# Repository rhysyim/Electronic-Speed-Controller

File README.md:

A hardware implementation using comparators to compare BEMF of motor in /PCB/Triple Half Bridge Driver v4b2. The original implementatoin with current sensing amplifier in /PCB/Triple Half Bridge Driver v4a (footprints not in place yet).

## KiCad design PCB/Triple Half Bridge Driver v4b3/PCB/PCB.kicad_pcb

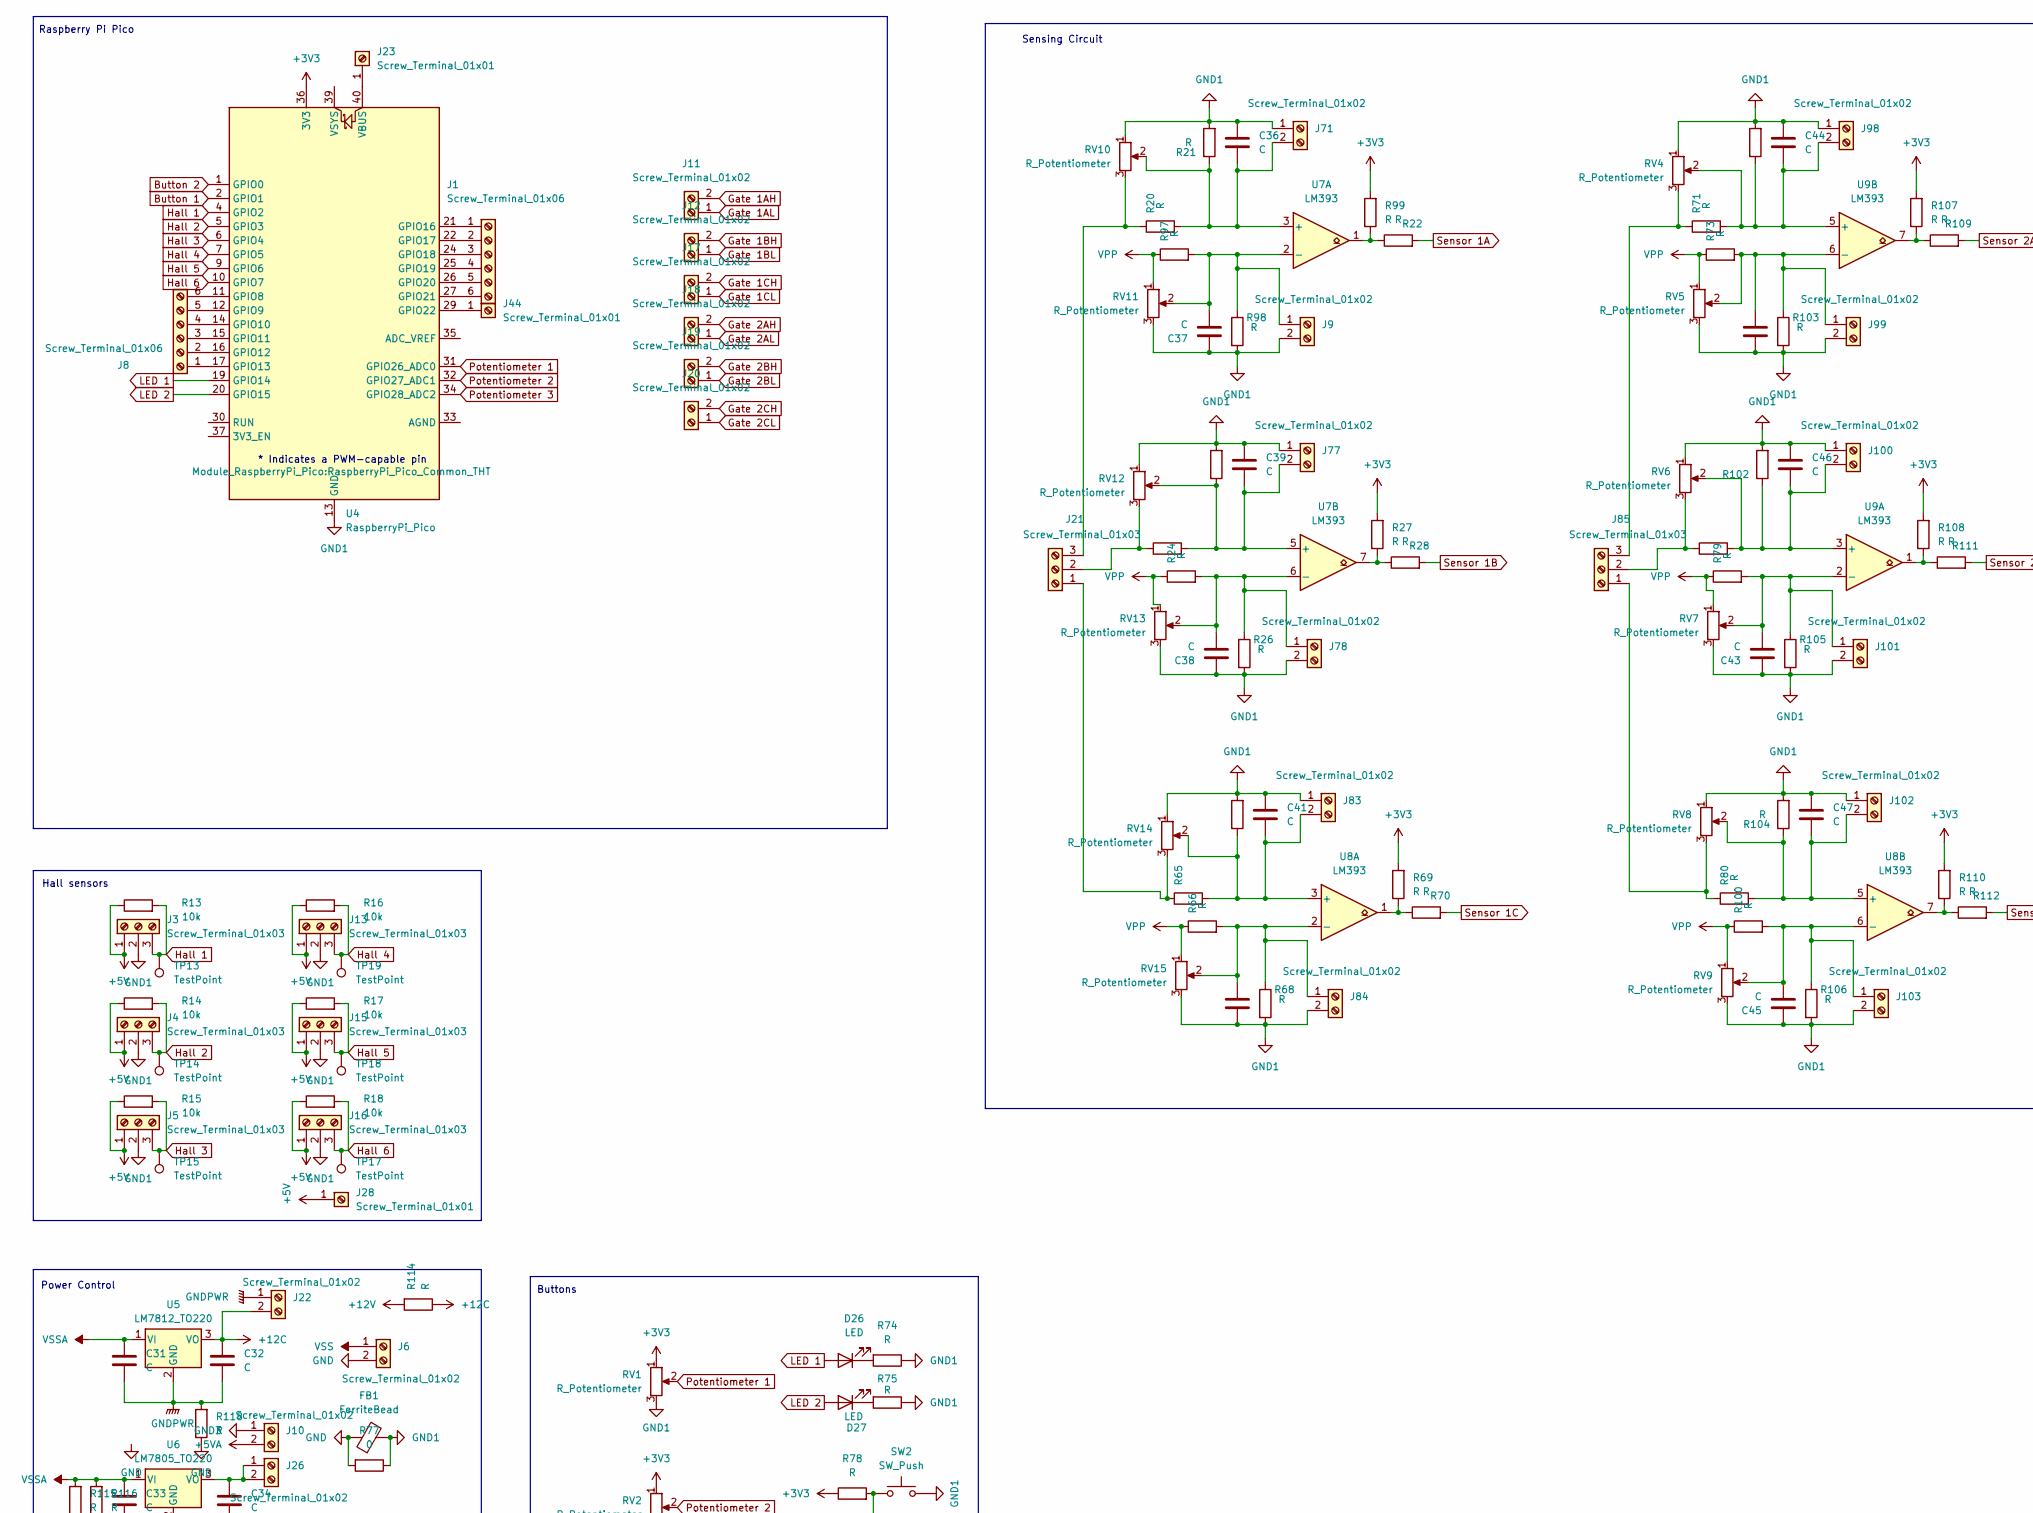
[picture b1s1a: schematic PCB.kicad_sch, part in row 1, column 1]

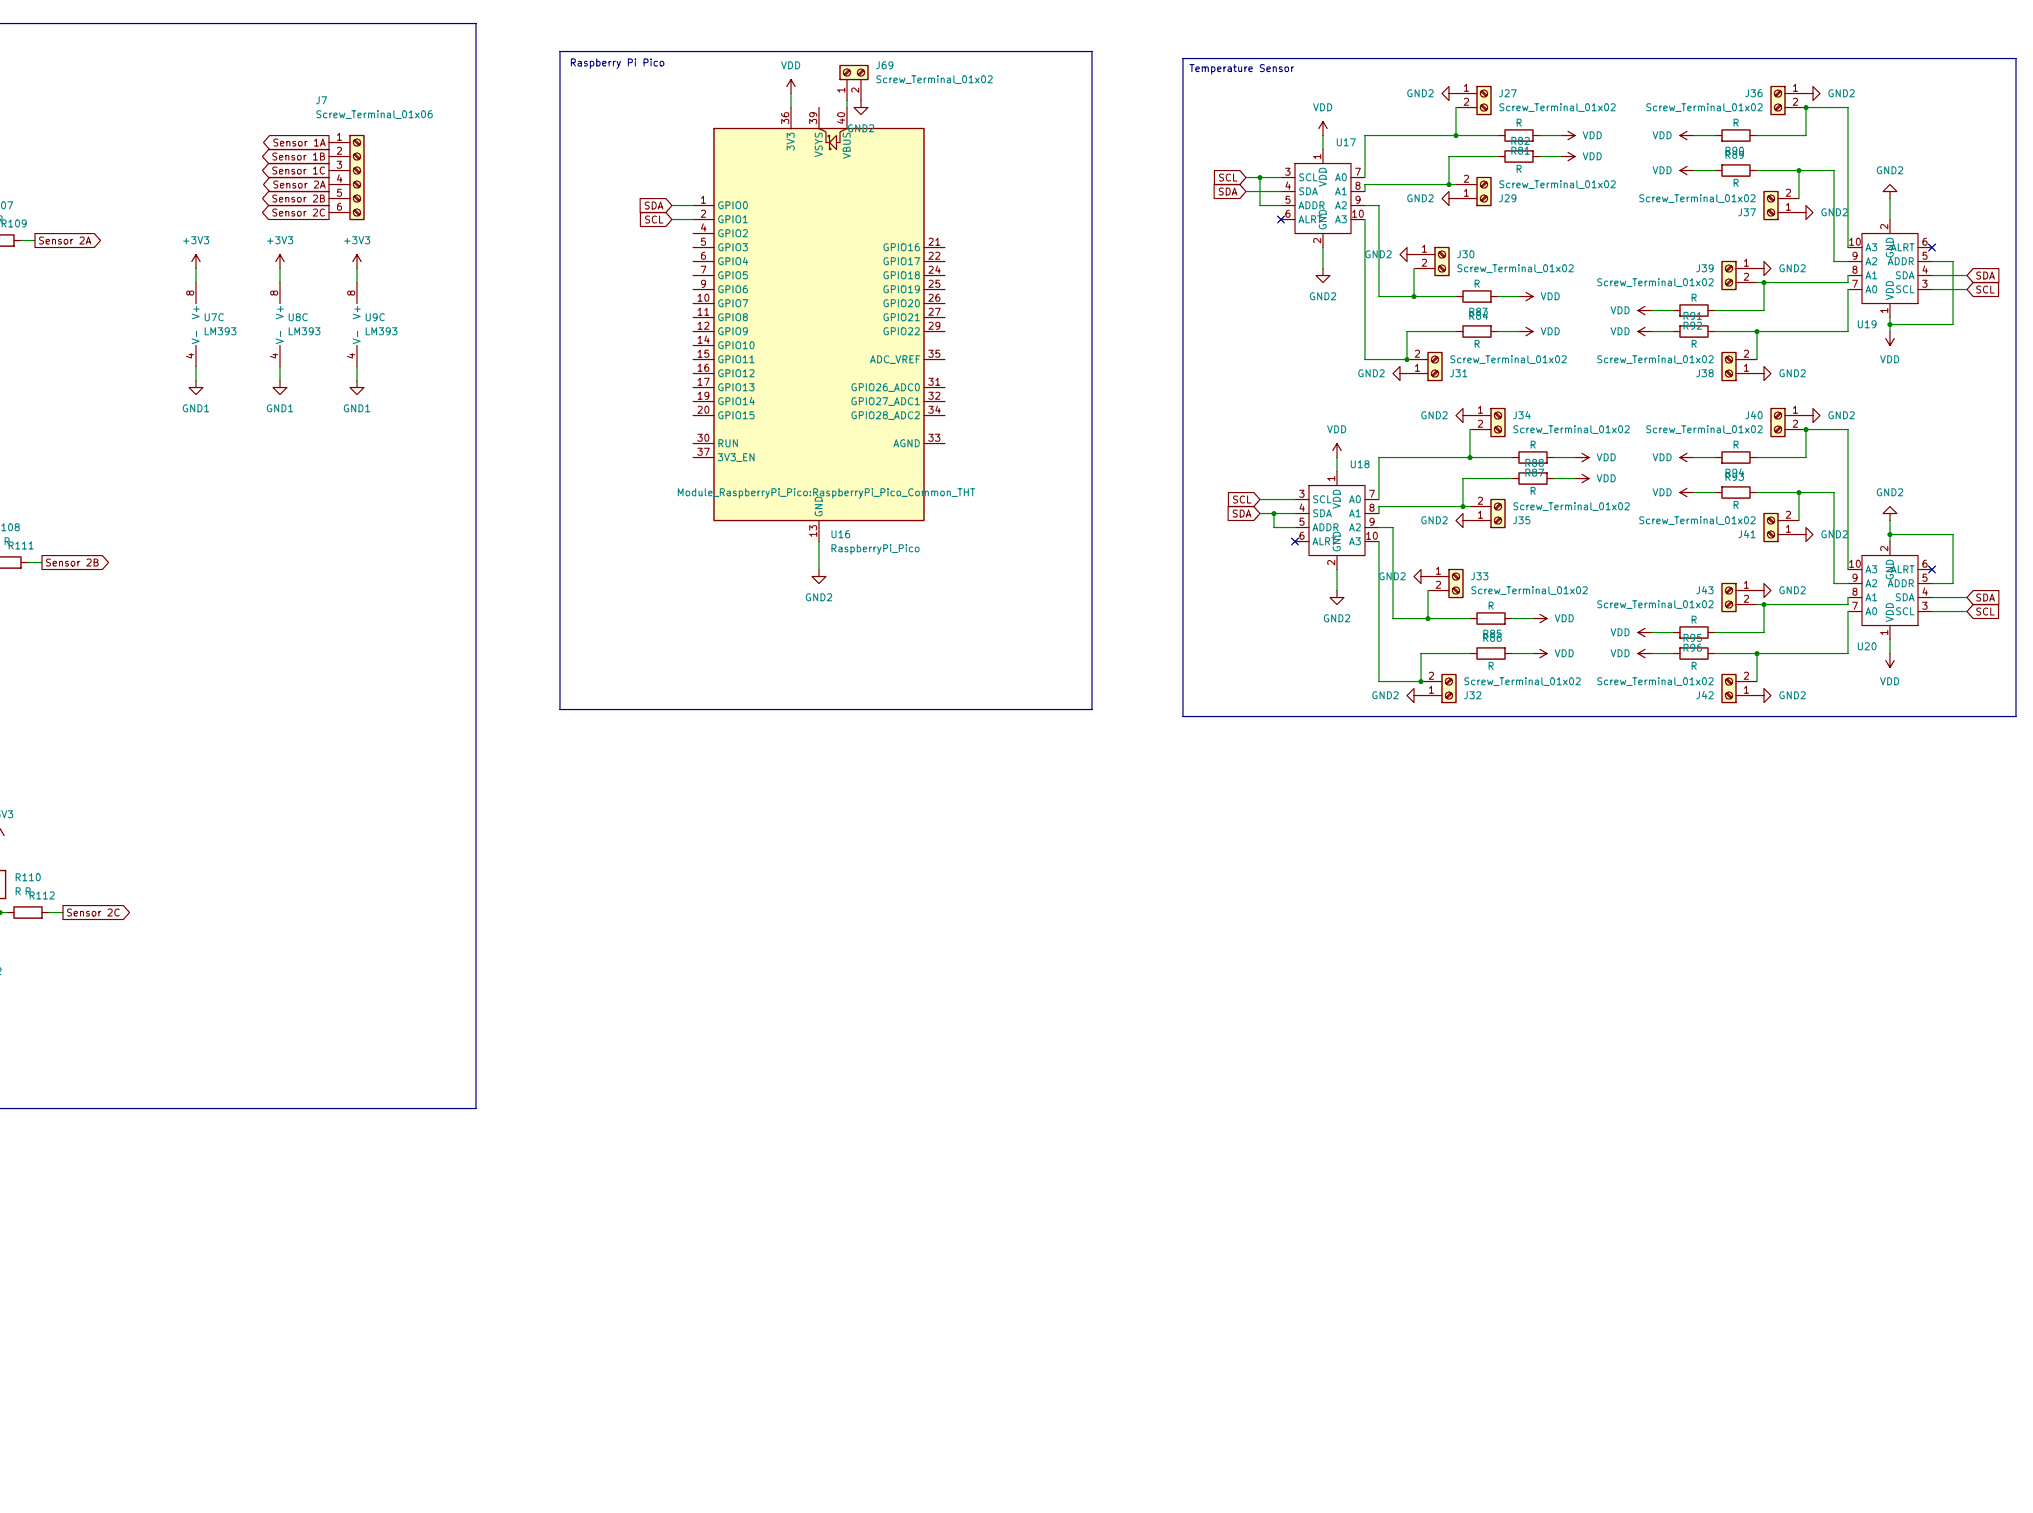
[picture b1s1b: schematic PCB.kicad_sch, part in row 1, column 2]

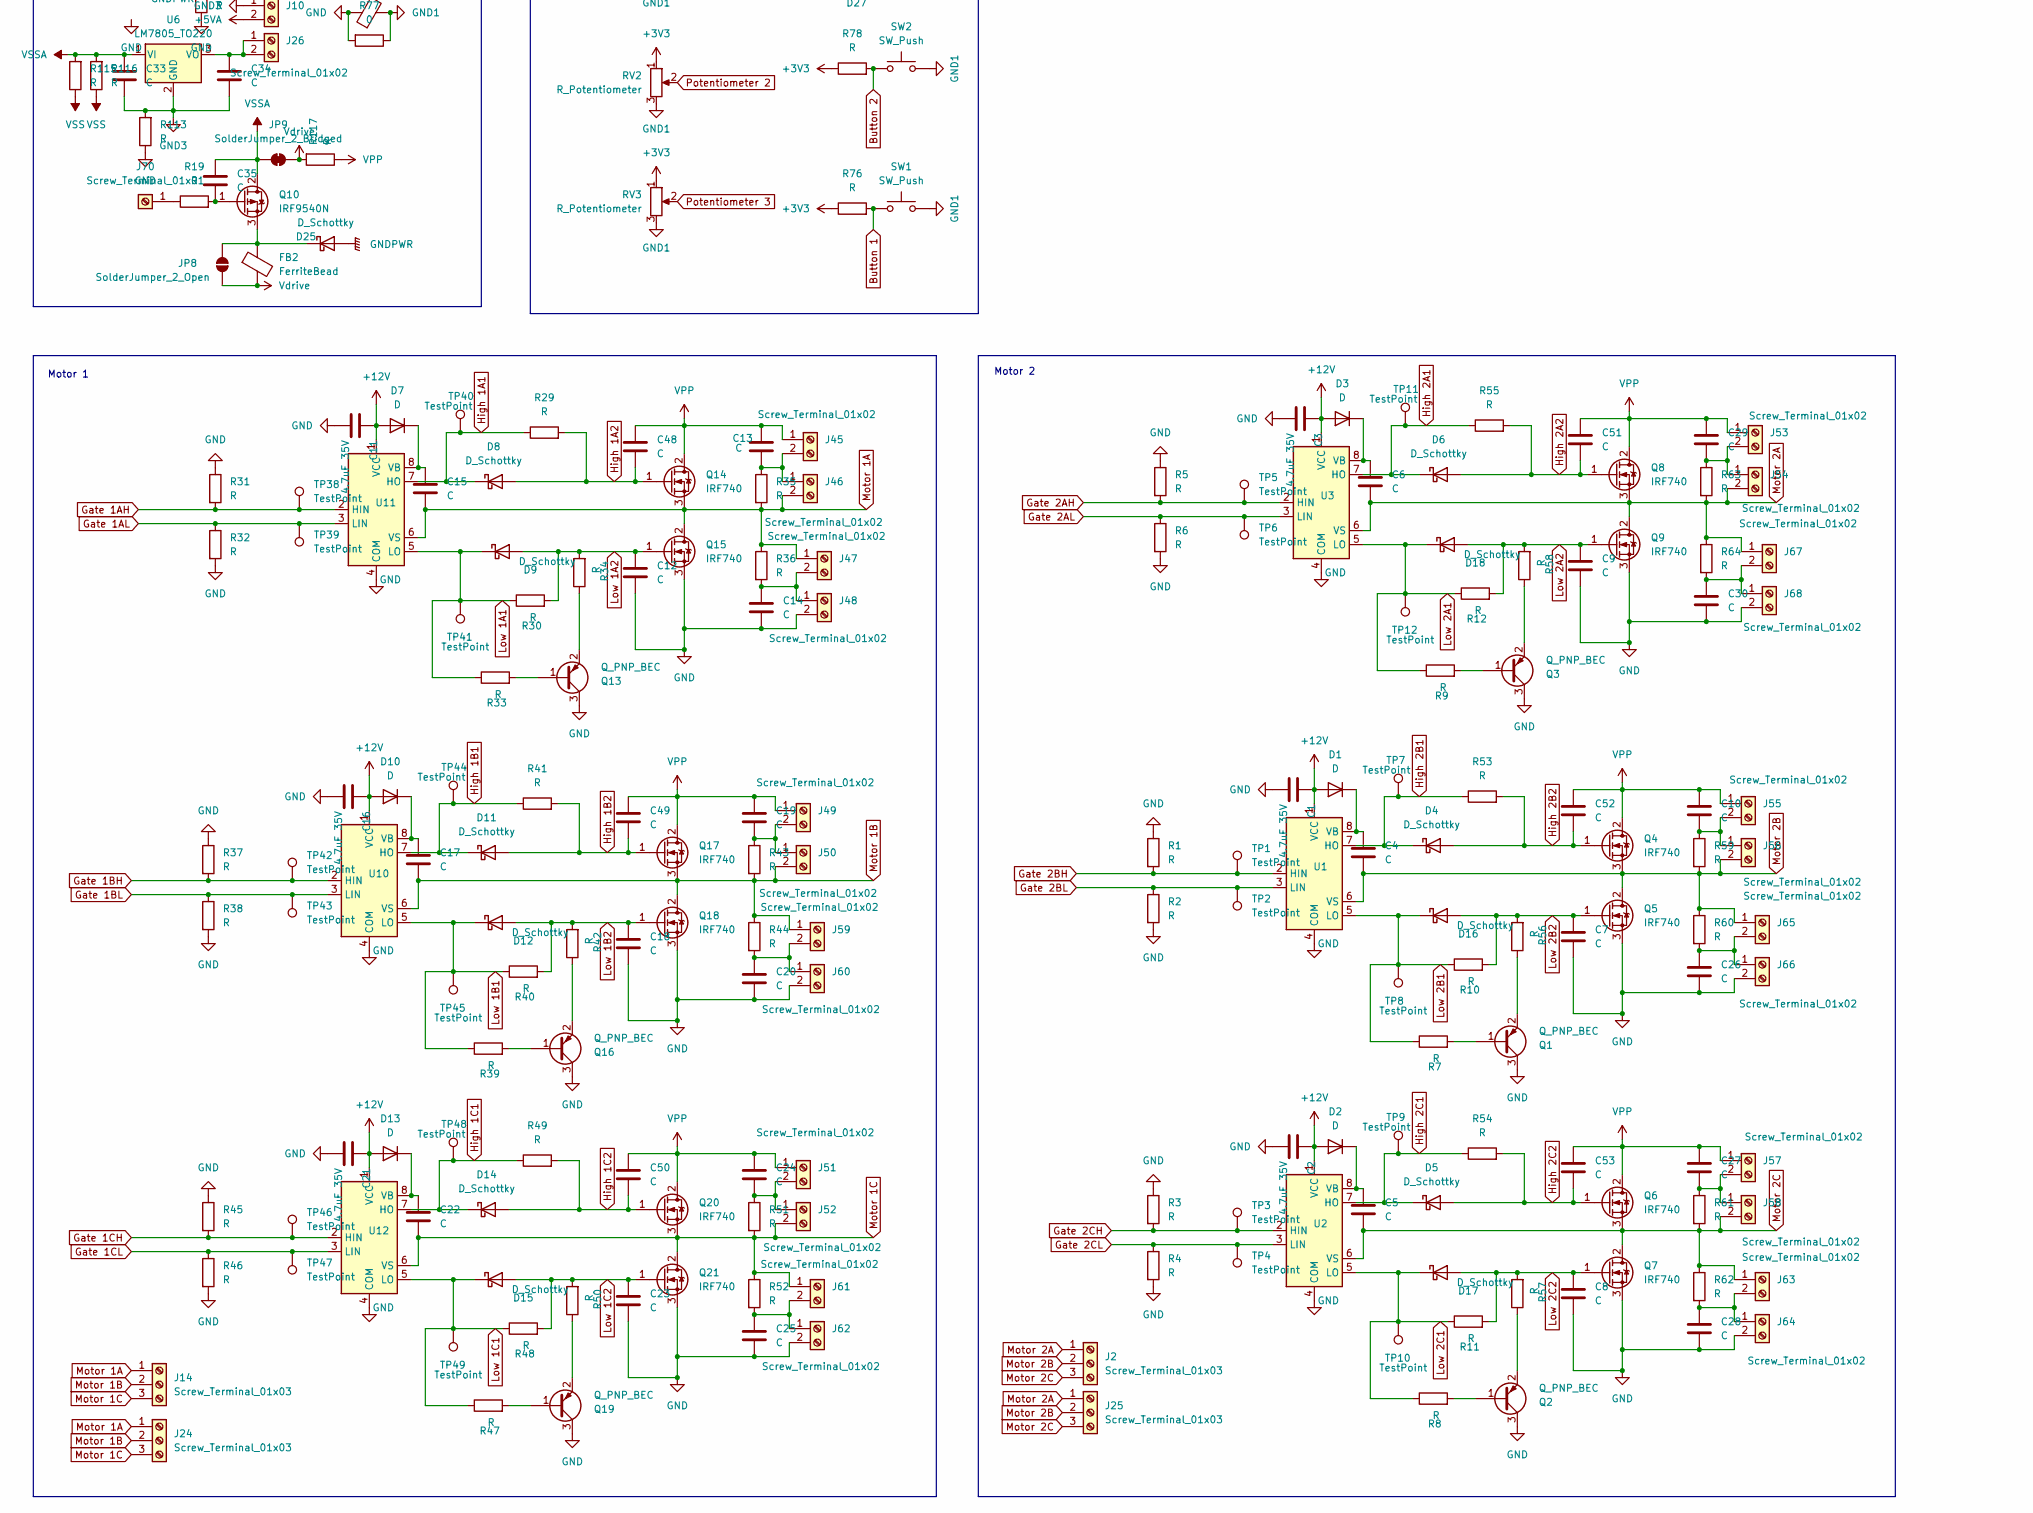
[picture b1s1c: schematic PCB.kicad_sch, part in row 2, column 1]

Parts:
C1, C2, C3, C11, C16, C21: 4.7uF 35V; C_Rect_L7.0mm_W4.5mm_P5.00mm; LCSC C162274
C4, C5, C6, C7, C8, C9, C10, C12, C13, C14, C15, C17, C18, C19, C20, C22, C23, C24, C25, C26, C27, C28, C29, C30, C31, C32, C33, C34, C35, C36, C37, C38, C39, C40, C41, C42, C43, C44, C45, C46, C47, C48, C49, C50, C51, C52, C53: C; C_Rect_L7.0mm_W4.5mm_P5.00mm
D1, D2, D3, D7, D10, D13: D; D_A-405_P7.62mm_Horizontal
D4, D5, D6, D8, D9, D11, D12, D14, D15, D16, D17, D18, D25: D_Schottky; D_A-405_P7.62mm_Horizontal
D26, D27: LED; LED_D5.0mm
FB1, FB2: FerriteBead; LairdTech_28C0236-0JW-10
J1, J7, J8: Screw_Terminal_01x06; PinHeader_1x06_P2.54mm_Vertical
J2, J14, J21, J24, J25, J85: Screw_Terminal_01x03; 1792876
J3, J4, J5, J13, J15, J16: Screw_Terminal_01x03; PinHeader_1x03_P2.54mm_Vertical
J6, J9, J10, J11, J12, J17, J18, J19, J20, J22, J69: Screw_Terminal_01x02; 1792863
J23, J44, J70: Screw_Terminal_01x01; PinHeader_1x01_P2.54mm_Vertical
J26: Screw_Terminal_01x02; PinHeader_1x02_P2.54mm_Vertical
J27, J29, J30, J31, J32, J33, J34, J35, J36, J37, J38, J39, J40, J41, J42, J43, J45, J46, J47, J48, J49, J50, J51, J52, J53, J54, J55, J56, J57, J58, J59, J60, J61, J62, J63, J64, J65, J66, J67, J68, J71, J77, J78, J83, J84, J98, J99, J100, J101, J102, J103: Screw_Terminal_01x02; TerminalBlock_4Ucon_1x02_P3.50mm_Horizontal
J28: Screw_Terminal_01x01; TerminalBlock_4Ucon_1x02_P3.50mm_Horizontal
JP8: SolderJumper_2_Open; SolderJumper-2_P1.3mm_Open_Pad1.0x1.5mm
JP9: SolderJumper_2_Bridged; SolderJumper-2_P1.3mm_Bridged_Pad1.0x1.5mm
Q1, Q2, Q3, Q13, Q16, Q19: Q_PNP_BEC; TO-220-3_Vertical; LCSC C686646
Q4, Q5, Q6, Q7, Q8, Q9, Q14, Q15, Q17, Q18, Q20, Q21: IRF740; TO-220-3_Vertical
Q10: IRF9540N; TO-220-3_Vertical
R1, R2, R3, R4, R5, R6, R7, R8, R9, R10, R11, R12, R19, R20, R21, R22, R23, R24, R25, R26, R27, R28, R29, R30, R31, R32, R33, R34, R35, R36, R37, R38, R39, R40, R41, R42, R43, R44, R45, R46, R47, R48, R49, R50, R51, R52, R53, R54, R55, R56, R57, R58, R59, R60, R61, R62, R63, R64, R65, R66, R67, R68, R69, R70, R71, R72, R73, R74, R75, R76, R78, R79, R80, R81, R82, R83, R84, R85, R86, R87, R88, R89, R90, R91, R92, R93, R94, R95, R96, R97, R98, R99, R100, R101, R102, R103, R104, R105, R106, R107, R108, R109, R110, R111, R112, R113, R114, R115, R116, R117, R118: R; R_Axial_DIN0207_L6.3mm_D2.5mm_P7.62mm_Horizontal
R13, R14, R15, R16, R17, R18: 10k; R_Axial_DIN0207_L6.3mm_D2.5mm_P7.62mm_Horizontal
R77: 0; R_Axial_DIN0207_L6.3mm_D2.5mm_P7.62mm_Horizontal
RV1, RV2, RV3, RV4, RV5, RV6, RV7, RV8, RV9, RV10, RV11, RV12, RV13, RV14, RV15: R_Potentiometer; Potentiometer_Alps_RK09K_Single_Vertical
SW1, SW2: SW_Push; SW_PUSH_6mm_H8.5mm
TP1, TP2, TP3, TP4, TP5, TP6, TP7, TP8, TP9, TP10, TP11, TP12, TP13, TP14, TP15, TP17, TP18, TP19, TP38, TP39, TP40, TP41, TP42, TP43, TP44, TP45, TP46, TP47, TP48, TP49: TestPoint; TestPoint_THTPad_2.0x2.0mm_Drill1.0mm
U1, U2, U3, U10, U11, U12: IRS2101; DIP-8_W7.62mm
U4, U16: RaspberryPi_Pico; RaspberryPi_Pico_Common_THT
U5: LM7812_TO220; TO-220-3_Vertical
U6: LM7805_TO220; TO-220-3_Vertical
U7, U8, U9: LM393; DIP-8_W7.62mm
U17, U18, U19, U20: Adafruit_ADS1115

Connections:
+3V3: R27.2, R69.2, R76.1, R78.1, R99.2, R107.2, R108.2, R110.2, RV1.1, RV2.1, RV3.1, U4.36 (3V3), U7.8 (V+), U8.8 (V+), U9.8 (V+)
+5V: J3.1, J4.1, J5.1, J13.1, J15.1, J16.1, J28.1, R13.1, R14.1, R15.1, R16.1, R17.1, R18.1
+5VA: J10.2
+12C: C32.1, J22.2, R114.1, U5.3 (VO)
+12V: C1.1, C2.1, C3.1, C11.1, C16.1, C21.1, D1.2 (A), D2.2 (A), D3.2 (A), D7.2 (A), D10.2 (A), D13.2 (A), R114.2, U1.1 (VCC), U2.1 (VCC), U3.1 (VCC), U10.1 (VCC), U11.1 (VCC), U12.1 (VCC)
Button 1: R76.2, SW1.1, U4.2 (GPIO1)
Button 2: R78.2, SW2.1, U4.1 (GPIO0)
GND: C1.2, C2.2, C3.2, C7.2, C8.2, C9.2, C11.2, C12.2, C14.2, C16.2, C18.2, C20.2, C21.2, C23.2, C25.2, C26.2, C28.2, C30.2, FB1.1, J6.2, J48.2, J60.2, J62.2, J64.2, J66.2, J68.2, Q1.3 (C), Q2.3 (C), Q3.3 (C), Q5.3 (S), Q7.3 (S), Q9.3 (S), Q13.3 (C), Q15.3 (S), Q16.3 (C), Q18.3 (S), Q19.3 (C), Q21.3 (S), R1.1, R2.2, R3.1, R4.2, R5.1, R6.2, R31.1, R32.2, R37.1, R38.2, R45.1, R46.2, R77.2, R113.1, R118.1, U1.4 (COM), U2.4 (COM), U3.4 (COM), U10.4 (COM), U11.4 (COM), U12.4 (COM)
GND1: C36.1, C37.1, C38.1, C39.1, C40.1, C41.1, C42.1, C43.1, C44.1, C45.1, C46.1, C47.1, FB1.2, J3.2, J4.2, J5.2, J9.2, J13.2, J15.2, J16.2, J71.1, J77.1, J78.2, J83.1, J84.2, J98.1, J99.2, J100.1, J101.2, J102.1, J103.2, R21.2, R25.2, R26.2, R67.2, R68.2, R74.1, R75.1, R77.1, R98.2, R101.2, R102.2, R103.2, R104.2, R105.2, R106.2, RV1.3, RV2.3, RV3.3, RV4.1, RV5.3, RV6.1, RV7.3, RV8.1, RV9.3, RV10.1, RV11.3, RV12.1, RV13.3, RV14.1, RV15.3, SW1.2, SW2.2, U4.3 (GND), U4.8 (GND), U4.13 (GND), U4.18 (GND), U4.23 (GND), U4.28 (GND), U4.38 (GND), U7.4 (V-), U8.4 (V-), U9.4 (V-)
GND2: J27.1, J29.1, J30.1, J31.1, J32.1, J33.1, J34.1, J35.1, J36.1, J37.1, J38.1, J39.1, J40.1, J41.1, J42.1, J43.1, J69.2, U16.3 (GND), U16.8 (GND), U16.13 (GND), U16.18 (GND), U16.23 (GND), U16.28 (GND), U16.38 (GND), U17.2 (GND), U18.2 (GND), U19.2 (GND), U20.2 (GND), U20.5 (ADDR)
GND3: C33.2, C34.2, J10.1, R113.2, U6.2 (GND)
GNDPWR: C31.2, C32.2, D25.2 (A), J22.1, R118.2, U5.2 (GND)
Gate 1AH: J11.2, R31.2, TP38.1, U11.2 (HIN)
Gate 1AL: J11.1, R32.1, TP39.1, U11.3 (LIN)
Gate 1BH: J12.2, R37.2, TP42.1, U10.2 (HIN)
Gate 1BL: J12.1, R38.1, TP43.1, U10.3 (LIN)
Gate 1CH: J17.2, R45.2, TP46.1, U12.2 (HIN)
Gate 1CL: J17.1, R46.1, TP47.1, U12.3 (LIN)
Gate 2AH: J18.2, R5.2, TP5.1, U3.2 (HIN)
Gate 2AL: J18.1, R6.1, TP6.1, U3.3 (LIN)
Gate 2BH: J19.2, R1.2, TP1.1, U1.2 (HIN)
Gate 2BL: J19.1, R2.1, TP2.1, U1.3 (LIN)
Gate 2CH: J20.2, R3.2, TP3.1, U2.2 (HIN)
Gate 2CL: J20.1, R4.1, TP4.1, U2.3 (LIN)
Hall 1: J3.3, R13.2, TP13.1, U4.4 (GPIO2)
Hall 2: J4.3, R14.2, TP14.1, U4.5 (GPIO3)
Hall 3: J5.3, R15.2, TP15.1, U4.6 (GPIO4)
Hall 4: J13.3, R16.2, TP19.1, U4.7 (GPIO5)
Hall 5: J15.3, R17.2, TP18.1, U4.9 (GPIO6)
Hall 6: J16.3, R18.2, TP17.1, U4.10 (GPIO7)
High 1A1: D8.1 (K), R29.1, TP40.1, U11.7 (HO)
High 1A2: C48.2, D8.2 (A), Q14.1 (G), R29.2
High 1B1: D11.1 (K), R41.1, TP44.1, U10.7 (HO)
High 1B2: C49.2, D11.2 (A), Q17.1 (G), R41.2
High 1C1: D14.1 (K), R49.1, TP48.1, U12.7 (HO)
High 1C2: C50.2, D14.2 (A), Q20.1 (G), R49.2
High 2A1: D6.1 (K), R55.1, TP11.1, U3.7 (HO)
High 2A2: C51.2, D6.2 (A), Q8.1 (G), R55.2
High 2B1: D4.1 (K), R53.1, TP7.1, U1.7 (HO)
High 2B2: C52.2, D4.2 (A), Q4.1 (G), R53.2
High 2C1: D5.1 (K), R54.1, TP9.1, U2.7 (HO)
High 2C2: C53.2, D5.2 (A), Q6.1 (G), R54.2
LED 1: D26.2 (A), U4.19 (GPIO14)
LED 2: D27.2 (A), U4.20 (GPIO15)
Low 1A1: D9.1 (K), R30.1, R33.1, TP41.1, U11.5 (LO)
Low 1A2: C12.1, D9.2 (A), Q15.1 (G), R30.2, R34.2
Low 1B1: D12.1 (K), R39.1, R40.1, TP45.1, U10.5 (LO)
Low 1B2: C18.1, D12.2 (A), Q18.1 (G), R40.2, R42.2
Low 1C1: D15.1 (K), R47.1, R48.1, TP49.1, U12.5 (LO)
Low 1C2: C23.1, D15.2 (A), Q21.1 (G), R48.2, R50.2
Low 2A1: D18.1 (K), R9.1, R12.1, TP12.1, U3.5 (LO)
Low 2A2: C9.1, D18.2 (A), Q9.1 (G), R12.2, R58.2
Low 2B1: D16.1 (K), R7.1, R10.1, TP8.1, U1.5 (LO)
Low 2B2: C7.1, D16.2 (A), Q5.1 (G), R10.2, R56.2
Low 2C1: D17.1 (K), R8.1, R11.1, TP10.1, U2.5 (LO)
Low 2C2: C8.1, D17.2 (A), Q7.1 (G), R11.2, R57.2
Motor 1A: C15.2, J14.1, J24.1, J46.2, J47.1, Q14.3 (S), Q15.2 (D), R35.2, R36.1, U11.6 (VS)
Motor 1B: C17.2, J14.2, J24.2, J50.2, J59.1, Q17.3 (S), Q18.2 (D), R43.2, R44.1, U10.6 (VS)
Motor 1C: C22.2, J14.3, J24.3, J52.2, J61.1, Q20.3 (S), Q21.2 (D), R51.2, R52.1, U12.6 (VS)
Motor 2A: C6.2, J2.1, J25.1, J54.2, J67.1, Q8.3 (S), Q9.2 (D), R63.2, R64.1, U3.6 (VS)
Motor 2B: C4.2, J2.2, J25.2, J56.2, J65.1, Q4.3 (S), Q5.2 (D), R59.2, R60.1, U1.6 (VS)
Motor 2C: C5.2, J2.3, J25.3, J58.2, J63.1, Q6.3 (S), Q7.2 (D), R61.2, R62.1, U2.6 (VS)
unnamed: C4.1, D1.1 (K), U1.8 (VB)
unnamed: C5.1, D2.1 (K), U2.8 (VB)
unnamed: C6.1, D3.1 (K), U3.8 (VB)
unnamed: C15.1, D7.1 (K), U11.8 (VB)
unnamed: C17.1, D10.1 (K), U10.8 (VB)
unnamed: C22.1, D13.1 (K), U12.8 (VB)
unnamed: D25.1 (K), FB2.1, JP8.1 (A), Q10.3 (S)
unnamed: D26.1 (K), R74.2
unnamed: D27.1 (K), R75.2
unnamed: J1.1, U4.21 (GPIO16)
unnamed: J1.2, U4.22 (GPIO17)
unnamed: J1.3, U4.24 (GPIO18)
unnamed: J1.4, U4.25 (GPIO19)
unnamed: J1.5, U4.26 (GPIO20)
unnamed: J1.6, U4.27 (GPIO21)
unnamed: J8.1, U4.17 (GPIO13)
unnamed: J8.2, U4.16 (GPIO12)
unnamed: J8.3, U4.15 (GPIO11)
unnamed: J8.4, U4.14 (GPIO10)
unnamed: J8.5, U4.12 (GPIO9)
unnamed: J8.6, U4.11 (GPIO8)
unnamed: C37.2, J9.1, R97.2, R98.1, RV11.2, U7.2 (-)
unnamed: J21.1, R65.1, RV14.3
unnamed: J21.2, R23.1, RV12.3
unnamed: J21.3, R20.1, RV10.3
unnamed: J23.1, U4.40 (VBUS)
unnamed: C34.1, J26.1, J26.2, U6.3 (VO)
unnamed: J27.2, R81.1, U17.7 (A0)
unnamed: J29.2, R82.1, U17.8 (A1)
unnamed: J30.2, R83.1, U17.9 (A2)
unnamed: J31.2, R84.1, U17.10 (A3)
unnamed: J32.2, R86.1, U18.10 (A3)
unnamed: J33.2, R85.1, U18.9 (A2)
unnamed: J34.2, R87.1, U18.7 (A0)
unnamed: J35.2, R88.1, U18.8 (A1)
unnamed: J36.2, R90.1, U19.10 (A3)
unnamed: J37.2, R89.1, U19.9 (A2)
unnamed: J38.2, R91.1, U19.7 (A0)
unnamed: J39.2, R92.1, U19.8 (A1)
unnamed: J40.2, R94.1, U20.10 (A3)
unnamed: J41.2, R93.1, U20.9 (A2)
unnamed: J42.2, R95.1, U20.7 (A0)
unnamed: J43.2, R96.1, U20.8 (A1)
unnamed: J44.1, U4.29 (GPIO22)
unnamed: C13.2, J45.2, J46.1, R35.1
unnamed: C14.1, J47.2, J48.1, R36.2
unnamed: C19.2, J49.2, J50.1, R43.1
unnamed: C24.2, J51.2, J52.1, R51.1
unnamed: C29.2, J53.2, J54.1, R63.1
unnamed: C10.2, J55.2, J56.1, R59.1
unnamed: C27.2, J57.2, J58.1, R61.1
unnamed: C20.1, J59.2, J60.1, R44.2
unnamed: C25.1, J61.2, J62.1, R52.2
unnamed: C28.1, J63.2, J64.1, R62.2
unnamed: C26.1, J65.2, J66.1, R60.2
unnamed: C30.1, J67.2, J68.1, R64.2
unnamed: J69.1, U16.40 (VBUS)
unnamed: J70.1, R19.1
unnamed: C36.2, J71.2, R20.2, R21.1, RV10.2, U7.3 (+)
unnamed: C39.2, J77.2, R23.2, R25.1, RV12.2, U7.5 (+)
unnamed: C38.2, J78.1, R24.2, R26.1, RV13.2, U7.6 (-)
unnamed: C41.2, J83.2, R65.2, R67.1, RV14.2, U8.3 (+)
unnamed: C40.2, J84.1, R66.2, R68.1, RV15.2, U8.2 (-)
unnamed: J85.1, R80.1, RV8.3
unnamed: J85.2, R72.1, RV6.3
unnamed: J85.3, R71.1, RV4.3
unnamed: C44.2, J98.2, R71.2, R101.1, RV4.2, U9.5 (+)
unnamed: C42.2, J99.1, R73.2, R103.1, RV5.2, U9.6 (-)
unnamed: C46.2, J100.2, R72.2, R102.1, RV6.2, U9.3 (+)
unnamed: C43.2, J101.1, R79.2, R105.1, RV7.2, U9.2 (-)
unnamed: C47.2, J102.2, R80.2, R104.1, RV8.2, U8.5 (+)
unnamed: C45.2, J103.1, R100.2, R106.1, RV9.2, U8.6 (-)
unnamed: Q1.1 (B), R7.2
unnamed: Q1.2 (E), R56.1
unnamed: Q2.1 (B), R8.2
unnamed: Q2.2 (E), R57.1
unnamed: Q3.1 (B), R9.2
unnamed: Q3.2 (E), R58.1
unnamed: C35.2, Q10.1 (G), R19.2
unnamed: Q13.1 (B), R33.2
unnamed: Q13.2 (E), R34.1
unnamed: Q16.1 (B), R39.2
unnamed: Q16.2 (E), R42.1
unnamed: Q19.1 (B), R47.2
unnamed: Q19.2 (E), R50.1
unnamed: R22.1, R99.1, U7.1
unnamed: R27.1, R28.1, U7.7
unnamed: R69.1, R70.1, U8.1
unnamed: R107.1, R109.1, U9.7
unnamed: R108.1, R111.1, U9.1
unnamed: R110.1, R112.1, U8.7
Potentiometer 1: RV1.2, U4.31 (GPIO26_ADC0)
Potentiometer 2: RV2.2, U4.32 (GPIO27_ADC1)
Potentiometer 3: RV3.2, U4.34 (GPIO28_ADC2)
SCL: U16.2 (GPIO1), U17.3 (SCL), U17.5 (ADDR), U18.3 (SCL), U19.3 (SCL), U20.3 (SCL)
SDA: U16.1 (GPIO0), U17.4 (SDA), U18.4 (SDA), U18.5 (ADDR), U19.4 (SDA), U20.4 (SDA)
Sensor 1A: J7.1, R22.2
Sensor 1B: J7.2, R28.2
Sensor 1C: J7.3, R70.2
Sensor 2A: J7.4, R109.2
Sensor 2B: J7.5, R111.2
Sensor 2C: J7.6, R112.2
VDD: R81.2, R82.2, R83.2, R84.2, R85.2, R86.2, R87.2, R88.2, R89.2, R90.2, R91.2, R92.2, R93.2, R94.2, R95.2, R96.2, U16.36 (3V3), U17.1 (VDD), U18.1 (VDD), U19.1 (VDD), U19.5 (ADDR), U20.1 (VDD)
VPP: C10.1, C13.1, C19.1, C24.1, C27.1, C29.1, C48.1, C49.1, C50.1, C51.1, C52.1, C53.1, J45.1, J49.1, J51.1, J53.1, J55.1, J57.1, Q4.2 (D), Q6.2 (D), Q8.2 (D), Q14.2 (D), Q17.2 (D), Q20.2 (D), R24.1, R66.1, R73.1, R79.1, R97.1, R100.1, R117.1, RV5.1, RV7.1, RV9.1, RV11.1, RV13.1, RV15.1
VSS: J6.1, R115.1, R116.1
VSSA: C31.1, C33.1, C35.1, JP9.1 (A), Q10.2 (D), R115.2, R116.2, U5.1 (VI), U6.1 (VI)
Vdrive: FB2.2, JP8.2 (B), JP9.2 (B), R117.2

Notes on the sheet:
Raspberry Pi Pico
Power Control
Temperature Sensor
Buttons
Sensing Circuit
Motor 2
* Indicates a PWM-capable pin
Hall sensors
Motor 1

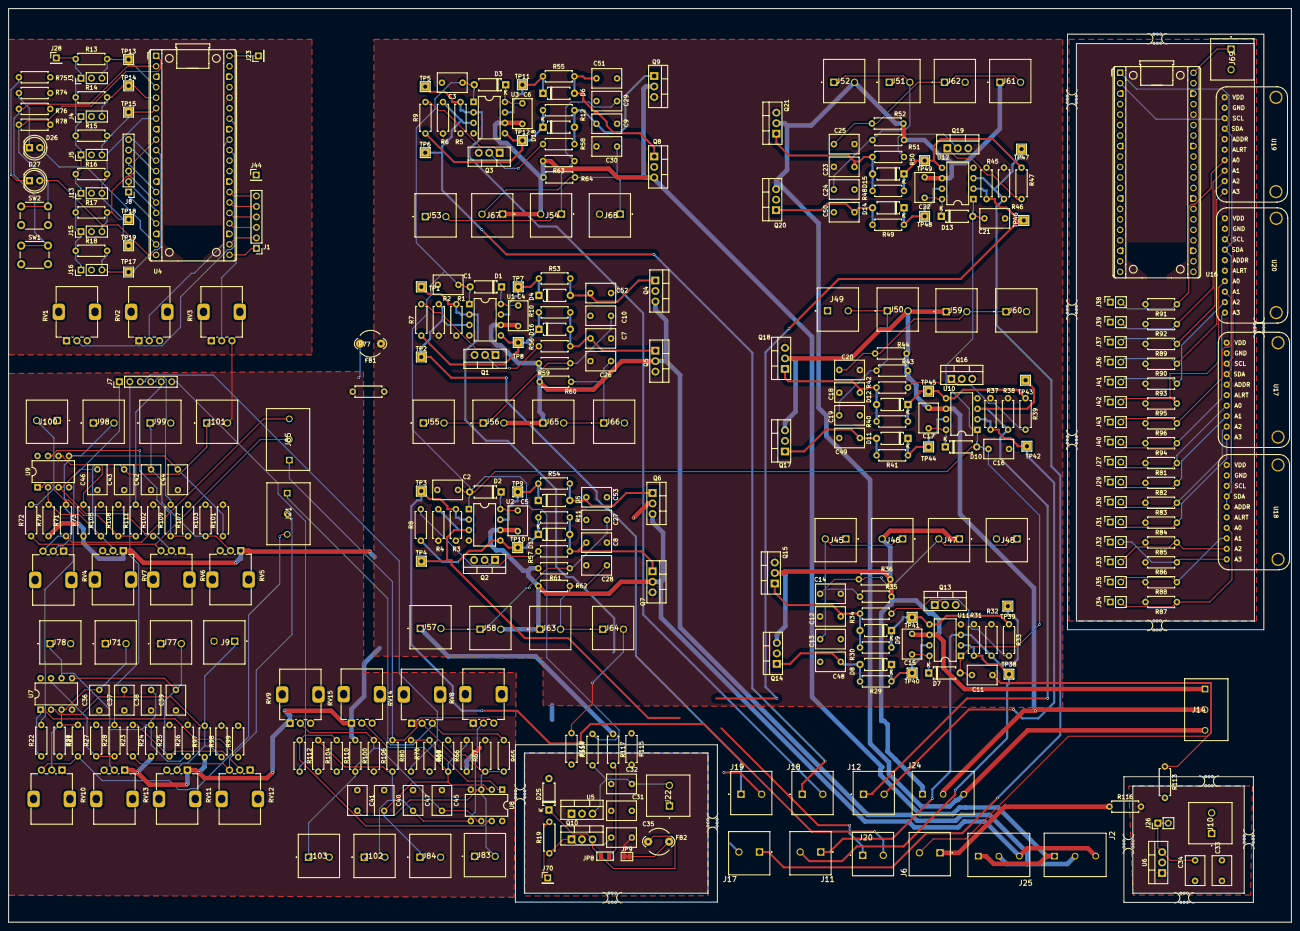
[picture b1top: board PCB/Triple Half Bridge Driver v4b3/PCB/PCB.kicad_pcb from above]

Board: 2 copper layers, 311.0 x 221.5 mm, 374 parts (0 on the bottom side), 168 nets.

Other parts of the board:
mouse-bite-2.54mm-slot, mouse-bite-2.54mm-slot2, mouse-bite-2.54mm-slot3, mouse-bite-2.54mm-slot4, mouse-bite-2.54mm-slot4#2, mouse-bite-2.54mm-slot4#3, mouse-bite-2.54mm-slot5, mouse-bite-2.54mm-slot7, mouse-bite-2.54mm-slot8, mouse-bite-2.54mm-slot8#2, mouse-bite-2.54mm-slot8#3, mouse-bite-2.54mm-slot8#4, mouse-bite-2.54mm-slot9: VAL**; mouse-bite-2.54mm-slot
